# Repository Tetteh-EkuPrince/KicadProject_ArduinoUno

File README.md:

# KicadProject_ArduinoUno
This repository contains the KiCad schematic, PCB layout files, BOM, and generated Gerber/Drill files for the Arduino Uno project.

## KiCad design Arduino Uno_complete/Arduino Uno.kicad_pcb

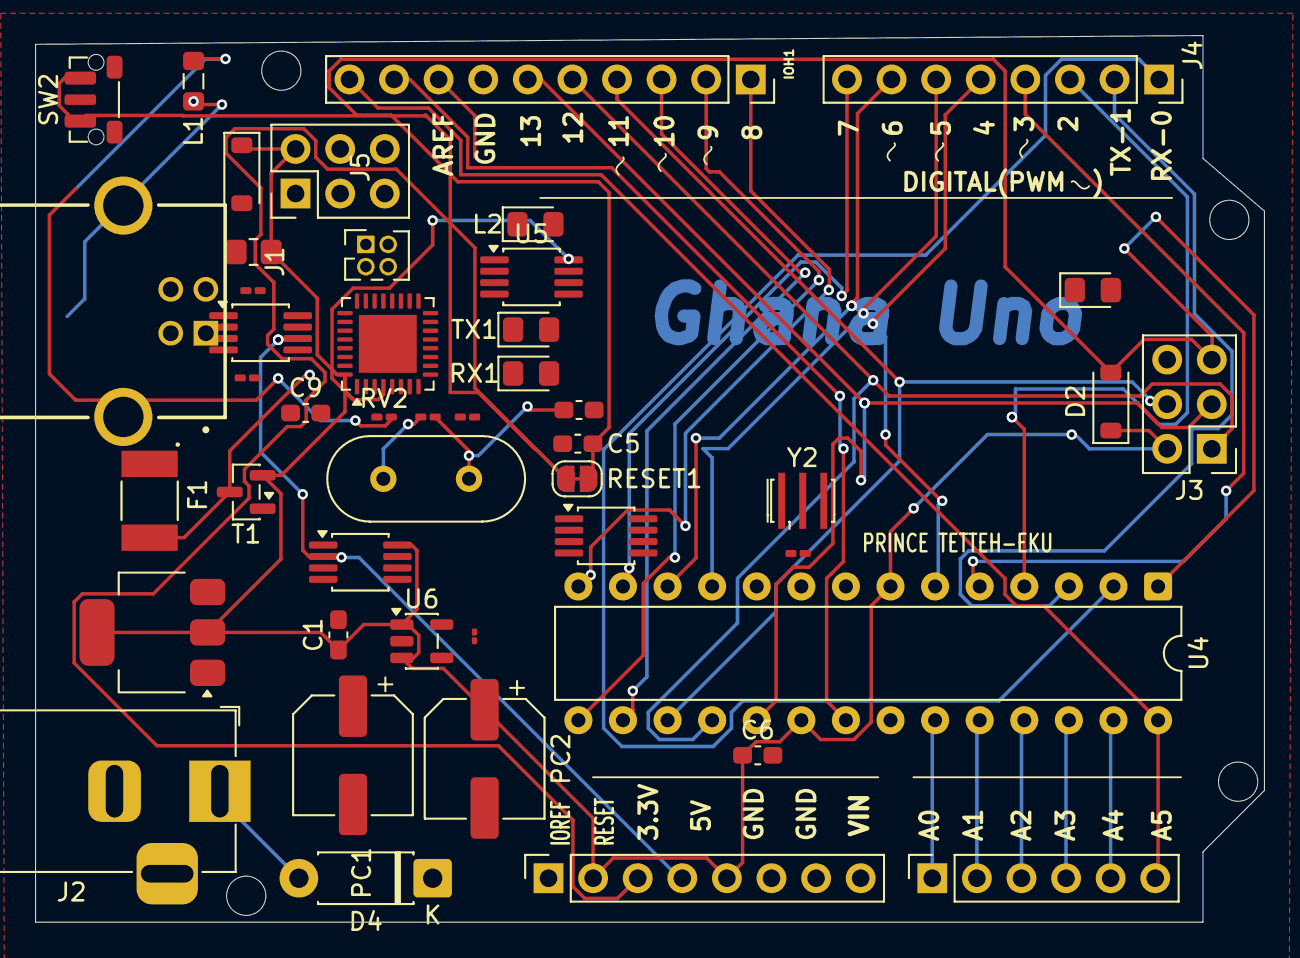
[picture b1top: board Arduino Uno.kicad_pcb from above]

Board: 2 copper layers, 70.0 x 50.5 mm, 46 parts (0 on the bottom side), 55 nets.

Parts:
AD1: 6X1F-H8.5; PinSocket_1x06_P2.54mm_Vertical
C1, C6: 100n; C_0603_1608Metric_Pad1.08x0.95mm_HandSolder
C3: 1u; C_01005_0402Metric
C5: 100N; C_0603_1608Metric_Pad1.08x0.95mm_HandSolder
C9, C11: 22p; C_0603_1608Metric_Pad1.08x0.95mm_HandSolder
D2: 1N914; D_SOD-123
D3: CD1206-S01575; D_SOD-123
D4: 1N4007; D_DO-41_SOD81_P7.62mm_Horizontal
F1: MF-MSMF050-2; FUSM4632X85
GREEN1: ON; LED_0805_2012Metric_Pad1.15x1.40mm_HandSolder
IOH1: 10X1F-H8.5; PinSocket_1x10_P2.54mm_Vertical
J1: USB_B; USB-B-S-X-X-TH
J2: Barrel_Jack_MountingPin; BarrelJack_Horizontal
J3, J5: Conn_02x03_Odd_Even; PinHeader_2x03_P2.54mm_Vertical
J4, J6: Conn_01x08; PinSocket_1x08_P2.54mm_Vertical
J8: Conn_02x02_Odd_Even; PinHeader_2x02_P1.27mm_Vertical
L1: BLM21; L_0805_2012Metric_Pad1.05x1.20mm_HandSolder
L2: YELLOW; LED_0805_2012Metric_Pad1.15x1.40mm_HandSolder
PC1, PC2: 47u; CP_Elec_6.3x5.4
R1: 1M; R_0201_0603Metric_Pad0.64x0.40mm_HandSolder
R2: R; R_0201_0603Metric_Pad0.64x0.40mm_HandSolder
RESET1: SolderJumper_2_Open; SolderJumper-2_P1.3mm_Open_RoundedPad1.0x1.5mm
RN1C1: 10K; R_0805_2012Metric_Pad1.20x1.40mm_HandSolder
RN3A1, RN3D1: 22R; R_0201_0603Metric_Pad0.64x0.40mm_HandSolder
RV2, RV3: Varistor; R_0201_0603Metric_Pad0.64x0.40mm_HandSolder
RX1: YELLOW; LED_0805_2012Metric_Pad1.15x1.40mm_HandSolder
SW2: SW_Push_Shielded; SW_Push_1P1T-MP_NO_Horizontal_Alps_SKRTLAE010
T1: FDN340P; SOT-23
TX1: YELLOW; LED_0805_2012Metric_Pad1.15x1.40mm_HandSolder
U2: NCP1117-3.3_SOT223; SOT-223-3_TabPin2
U3: ATmega16U2-M; QFN-32-1EP_5x5mm_P0.5mm_EP3.3x3.3mm
U4: ATmega328P-P; DIP-28_W7.62mm
U5, U5#2, U5#3, U7: LMV358; MSOP-8_3x3mm_P0.65mm
U6: LP2985-3.3; SOT-23-5
Y1: 16Hz; Crystal_HC49-4H_Vertical
Y2: Resonator_Small; Resonator_SMD_Murata_CSTxExxV-3Pin_3.0x1.1mm_HandSoldering

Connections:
+3V3(2): J6.4, U5#3.2 (-), U7.6 (-)
+5V: C1.1, C6.1, D2.1 (K), D3.1 (K), J3.2, J5.2, J6.2, J6.5, PC2.1, RN1C1.2, T1.2 (S), U2.2 (VO), U3.4 (VCC), U3.32 (AVCC), U4.7 (VCC), U4.20 (AVCC), U5.8 (V+), U5#3.8 (V+), U6.1 (VIN), U6.3 (ON/~OFF)
/13: U5.6 (-), U5.7, U5#3.6 (-), U5#3.7
/CMP: U5#3.3 (+), U7.5 (+)
/D+: J1.3 (D+), RN3D1.1, RV2.1
/D-: J1.2 (D-), RN3A1.1, RV3.1
/RD+: RN3D1.2, U3.29 (D+)
/RD-: RN3A1.2, U3.30 (D-)
/XUSB: F1.1, J1.1 (VBUS)
AREF(21): IOH1.9, U4.21 (AREF)
GNDD: C1.2, C3.2, C6.2, C9.1, C11.1, GREEN1.1 (K), J2.2, J3.6, J5.6, J6.6, J6.7, L2.1 (K), PC1.2, PC2.2, SW2.2, U2.1 (GND), U3.3 (GND), U3.33 (GND), U4.8 (GND), U4.22 (AGND), U5.4 (V-), U5#3.4 (V-), U6.2 (GND), Y2.2
unnamed: AD1.1, U4.23 (PC0)
unnamed: AD1.2, U4.24 (PC1)
unnamed: AD1.3, U4.25 (PC2)
unnamed: AD1.4, U4.26 (PC3)
unnamed: AD1.5, U4.27 (PC4)
unnamed: C5.2, D2.2 (A), J3.5, J6.3, RESET1.1 (A), RESET1.2 (B), SW2.1, U4.1 (~RESET/PC6)
unnamed: D3.2 (A), J5.3, RN1C1.1, U3.15 (PB1)
unnamed: D4.2 (A), J2.1
unnamed: D4.1 (K), PC1.1, U2.3 (VI)
unnamed: J1.4 (GND), L1.2, U3.28 (UGND)
unnamed: IOH1.1, U4.14 (PB0)
unnamed: IOH1.2, U4.15 (PB1)
unnamed: IOH1.3, U4.16 (PB2)
unnamed: IOH1.4, J3.4, U4.17 (PB3)
unnamed: IOH1.5, J3.1, U4.18 (PB4)
unnamed: IOH1.6, J3.3, U4.19 (PB5)
unnamed: J1.SH (Shield), L1.1, RV2.2, RV3.2
unnamed: J4.1, U4.2 (PD0)
unnamed: J4.2, U4.3 (PD1)
unnamed: J4.3, U4.4 (PD2)
unnamed: J4.4, U4.5 (PD3)
unnamed: J4.5, U4.6 (PD4)
unnamed: J4.6, U4.11 (PD5)
unnamed: J4.7, U4.12 (PD6)
unnamed: J4.8, U4.13 (PD7)
unnamed: J5.1, U3.17 (PB3)
unnamed: J5.4, U3.16 (PB2)
unnamed: J5.5, U3.24 (PC1/~RESET)
unnamed: J8.1, U3.18 (PB4)
unnamed: J8.2, U3.20 (PB6)
unnamed: J8.3, U3.19 (PB5)
unnamed: J8.4, U3.21 (PB7)
unnamed: RX1.1 (K), U3.10 (PD4)
unnamed: T1.1 (G), U5#3.1, U7.7
unnamed: TX1.1 (K), U3.11 (PD5)
unnamed: C9.2, R1.1, U3.2 (PC0/XTAL2), Y1.1
unnamed: C11.2, R1.2, U3.1 (XTAL1), Y1.2
unnamed: C5.1, U3.13 (~HWB/PD7)
unnamed: R2.2, U4.9 (XTAL1/PB6), Y2.3
unnamed: R2.1, U4.10 (XTAL2/PB7), Y2.1
unnamed: C3.1, U6.5 (VOUT)
SCI: AD1.6, IOH1.10, U4.28 (PC5)
SCK: IOH1.7, U5.5 (+), U5#3.5 (+)
USBVCC: F1.2, T1.3 (D), U3.31 (UVCC)
